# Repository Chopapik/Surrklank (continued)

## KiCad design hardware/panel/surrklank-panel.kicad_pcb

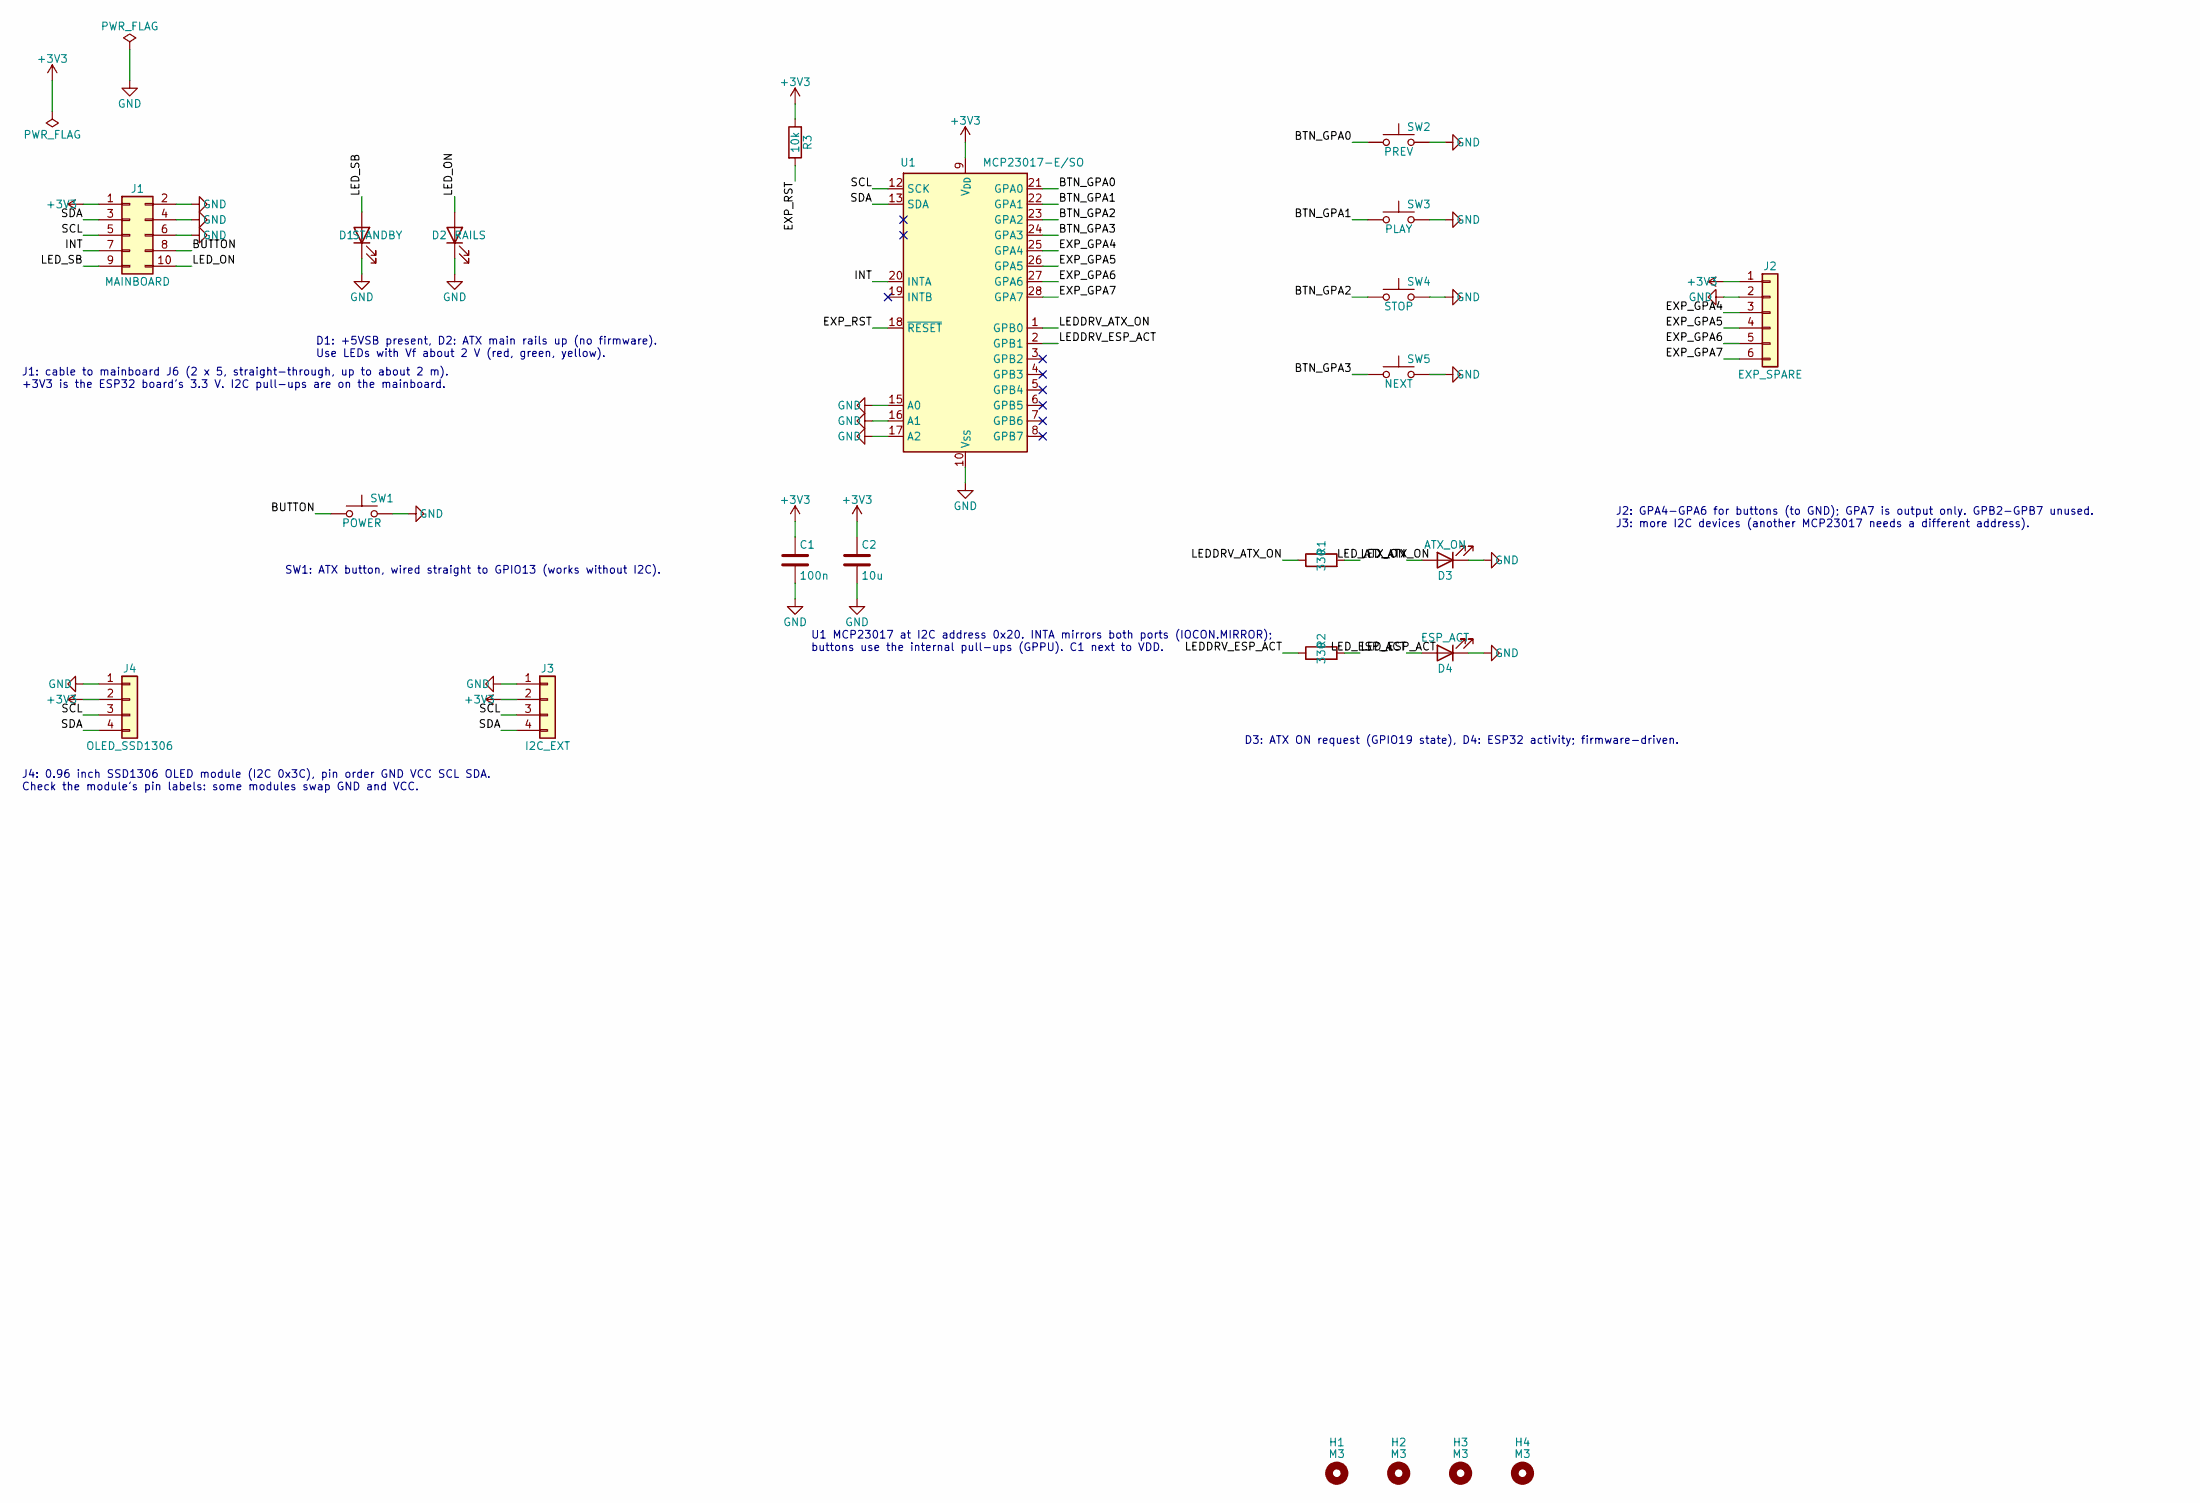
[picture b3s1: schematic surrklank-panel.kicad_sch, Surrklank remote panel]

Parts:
C1: 100n; C_0805_2012Metric
C2: 10u; C_0805_2012Metric
D1: STANDBY; LED_D3.0mm
D2: RAILS; LED_D3.0mm
D3: ATX_ON; LED_D3.0mm
D4: ESP_ACT; LED_D3.0mm
H1, H2, H3, H4: M3; MountingHole_3.2mm_M3
J1: MAINBOARD; IDC-Header_2x05_P2.54mm_Vertical
J2: EXP_SPARE; JST_XH_B6B-XH-A_1x06_P2.50mm_Vertical
J3: I2C_EXT; JST_XH_B4B-XH-A_1x04_P2.50mm_Vertical
J4: OLED_SSD1306; PinSocket_1x04_P2.54mm_Vertical
R1, R2: 330; R_0805_2012Metric
R3: 10k; R_0805_2012Metric
SW1: POWER; SW_PUSH_6mm
SW2: PREV; SW_PUSH_6mm
SW3: PLAY; SW_PUSH_6mm
SW4: STOP; SW_PUSH_6mm
SW5: NEXT; SW_PUSH_6mm
U1: MCP23017-E/SO; SOIC-28W_7.5x17.9mm_P1.27mm

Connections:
+3V3: C1.1, C2.1, J1.1, J2.1, J3.2, J4.2, R3.1, U1.9 (V_{DD})
/BTN_GPA0: SW2.1, U1.21 (GPA0)
/BTN_GPA1: SW3.1, U1.22 (GPA1)
/BTN_GPA2: SW4.1, U1.23 (GPA2)
/BTN_GPA3: SW5.1, U1.24 (GPA3)
/BUTTON: J1.8, SW1.1
/EXP_GPA4: J2.3, U1.25 (GPA4)
/EXP_GPA5: J2.4, U1.26 (GPA5)
/EXP_GPA6: J2.5, U1.27 (GPA6)
/EXP_GPA7: J2.6, U1.28 (GPA7)
/EXP_RST: R3.2, U1.18 (~RESET)
/INT: J1.7, U1.20 (INTA)
/LEDDRV_ATX_ON: R1.1, U1.1 (GPB0)
/LEDDRV_ESP_ACT: R2.1, U1.2 (GPB1)
/LED_ATX_ON: D3.2 (A), R1.2
/LED_ESP_ACT: D4.2 (A), R2.2
/LED_ON: D2.2 (A), J1.10
/LED_SB: D1.2 (A), J1.9
/SCL: J1.5, J3.3, J4.3, U1.12 (SCK)
/SDA: J1.3, J3.4, J4.4, U1.13 (SDA)
GND: C1.2, C2.2, D1.1 (K), D2.1 (K), D3.1 (K), D4.1 (K), J1.2, J1.4, J1.6, J2.2, J3.1, J4.1, SW1.2, SW2.2, SW3.2, SW4.2, SW5.2, U1.10 (V_{SS}), U1.15 (A0), U1.16 (A1), U1.17 (A2)

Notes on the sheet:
J1: cable to mainboard J6 (2 x 5, straight-through, up to about 2 m). +3V3 is the ESP32 board's 3.3 V. I2C pull-ups are on the mainboard.
D1: +5VSB present, D2: ATX main rails up (no firmware). Use LEDs with Vf about 2 V (red, green, yellow).
SW1: ATX button, wired straight to GPIO13 (works without I2C).
U1 MCP23017 at I2C address 0x20. INTA mirrors both ports (IOCON.MIRROR); buttons use the internal pull-ups (GPPU). C1 next to VDD.
D3: ATX ON request (GPIO19 state), D4: ESP32 activity; firmware-driven.
J4: 0.96 inch SSD1306 OLED module (I2C 0x3C), pin order GND VCC SCL SDA. Check the module's pin labels: some modules swap GND and VCC.
J2: GPA4-GPA6 for buttons (to GND); GPA7 is output only. GPB2-GPB7 unused. J3: more I2C devices (another MCP23017 needs a different address).

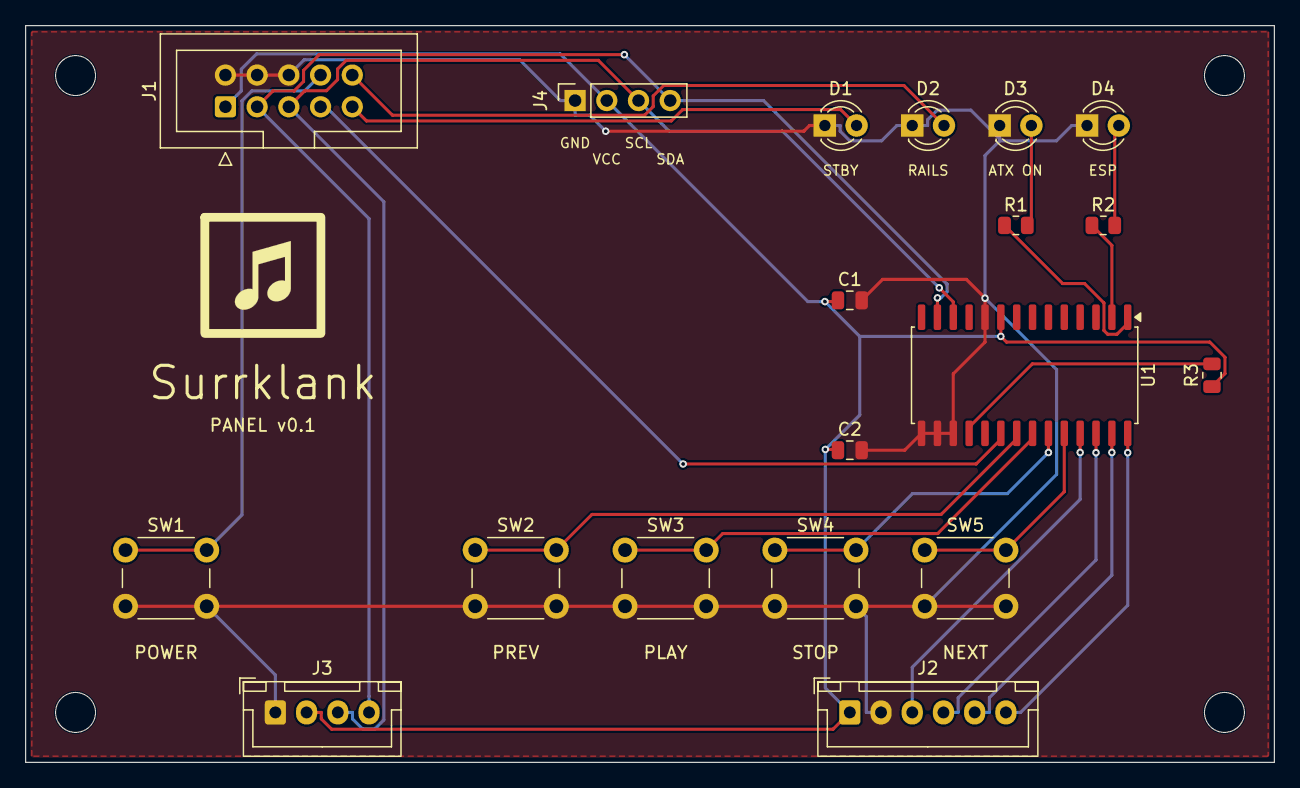
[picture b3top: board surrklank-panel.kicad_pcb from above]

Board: 2 copper layers, 100.0 x 59.0 mm, 25 parts (1 on the bottom side), 21 nets.

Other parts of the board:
LOGO1: Surrklank_Logo; Surrklank_Logo_8mm
LOGO2: Surrklank_Mark; Surrklank_Mark_10mm

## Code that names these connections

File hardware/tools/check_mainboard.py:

#!/usr/bin/env python3
"""Check an exported mainboard netlist against docs/WIRING.md (Mainboard).

Usage: python3 -I check_mainboard.py <netlist.xml>
Rules are written out here independently of the generator.
"""
import sys
import xml.etree.ElementTree as ET

# ESP32 board header (seller pin order; pins 1-19 left, 20-38 right, from the antenna end)
BOARD_PIN = {"GPIO23": "21", "GPIO22": "22", "GPIO34": "5", "GPIO17": "30", "GPIO16": "31",
             "GPIO35": "6", "GPIO18": "28", "GPIO21": "25", "GPIO33": "8", "GPIO32": "7",
             "GPIO19": "27", "GPIO13": "15", "GPIO36": "3", "3V3": "1", "5V": "19",
             "GPIO25": "9", "GPIO26": "10", "GPIO27": "11"}
# WIRING.md GPIO table: GPIO -> (branch connector or None, ribbon pin or role)
SIGNALS = {"GPIO23": ("J2", 1), "GPIO22": ("J2", 5), "GPIO34": ("J2", 13),
           "GPIO17": ("J3", 1), "GPIO16": ("J3", 5), "GPIO35": ("J3", 13)}
SHARED = {"GPIO18": 3, "GPIO21": 7, "GPIO33": 9, "GPIO32": 11}
PULL = {"GPIO21": "ESP_3V3", "GPIO33": "ESP_3V3", "GPIO18": "GND", "GPIO32": "GND",
        "GPIO22": "GND", "GPIO16": "GND", "GPIO23": "GND", "GPIO17": "GND",
        "GPIO34": "GND", "GPIO35": "GND", "GPIO13": "ESP_3V3", "GPIO27": "ESP_3V3"}
errors = []


def main(path):
    root = ET.parse(path).getroot()
    nets, where, func = {}, {}, {}
    for n in root.iter("net"):
        name = n.get("name").lstrip("/")  # local labels are exported as "/NAME"
        nodes = {(x.get("ref"), x.get("pin")) for x in n.iter("node")}
        nets[name] = nodes
        for x in n.iter("node"):
            where[(x.get("ref"), x.get("pin"))] = name
            func[(x.get("ref"), x.get("pin"))] = (x.get("pinfunction") or "").split("_")[0]

    def peers(ref, pin):
        return nets.get(where.get((ref, pin)), set()) - {(ref, pin)}

    def through(rn, pin):
        """Net on the other side of a resistor-array element."""
        return where.get((rn, str(9 - int(pin))))

    def gpio_net(g):
        return where.get(("A1", BOARD_PIN[g]))

    def reaches_via_series(g, conn, rpin):
        for r, q in peers("A1", BOARD_PIN[g]):
            if r.startswith("RN") and through(r, q) == where.get((conn, str(rpin))):
                return True
        return False

    def reaches_via_resistor(g, conn, rpin):
        """Single resistor between the GPIO and the connector pin (Q165 return)."""
        target = where.get((conn, str(rpin)))
        for r, q in peers("A1", BOARD_PIN[g]):
            if r.startswith("R") and not r.startswith("RN") \
                    and where.get((r, "2" if q == "1" else "1")) == target:
                return True
        return False

    for g, (conn, rpin) in SIGNALS.items():
        if rpin == 13:
            if not reaches_via_resistor(g, conn, rpin):
                errors.append(f"{g} must reach {conn}.13 (Q165) through a series resistor")
        elif not reaches_via_series(g, conn, rpin):
            errors.append(f"{g} must reach {conn}.{rpin} through a series resistor")
    for g, rpin in SHARED.items():
        for conn in ("J2", "J3"):
            if not reaches_via_series(g, conn, rpin):
                errors.append(f"{g} must reach {conn}.{rpin} through its own series resistor")
    for g, rail in PULL.items():
        rails = [through(r, q) for r, q in peers("A1", BOARD_PIN[g])
                 if r.startswith("RN") and through(r, q) in ("ESP_3V3", "GND")]
        if rails != [rail]:
            errors.append(f"{g}: expected one pull to {rail}, got {rails}")
    for conn in ("J2", "J3"):
        for p in range(2, 17, 2):
            if where.get((conn, str(p))) != "GND":
                errors.append(f"{conn}.{p} should be GND")
        if peers(conn, "15"):
            errors.append(f"{conn}.15 is a spare wire and must stay unconnected")

    if "+3V3" in nets or any(r.startswith("JP") and r != "JP1" for r, _ in where):
        errors.append("ATX +3V3 and the bench jumpers are removed")
    if gpio_net("3V3") != "ESP_3V3" or gpio_net("3V3") in ("+5V", "ATX_5VSB"):
        errors.append("ESP32 3V3 must stay separate from ATX +5V and +5VSB")
    # +5VSB path: terminal pin 4 -> removable jumper -> ESP32 5V, nothing else
    j1 = {p: where.get(("J1", p)) for p in "1234"}
    if [j1[p] for p in "1234"] != ["GND", "PS_ON#", "ATX_5VSB", "PWR_OK"] or ("J1", "5") in where:
        errors.append(f"J1 order wrong: {j1}")
    # +5VSB may also feed the panel standby LED resistor (checked below)
    on_5vsb = {(r, q) for r, q in nets.get("ATX_5VSB", set()) - {("J1", "3")}
               if r != "Q2" and not (r.startswith("R") and where.get((r, "2" if q == "1" else "1"))
                                     == where.get(("J6", "9")))}
    if len(on_5vsb) != 1 or not next(iter(on_5vsb))[0].startswith("JP"):
        errors.append(f"+5VSB must go only to one removable jumper, got {sorted(on_5vsb)}")
    else:
        jp = next(iter(on_5vsb))[0]
        if "ESP_5V" not in {where.get((jp, q)) for q in ("1", "2")}:
            errors.append("+5VSB jumper must lead to ESP32 5V")
    if gpio_net("5V") != "ESP_5V":
        errors.append("ESP32 5V pin must be on ESP_5V")
    # PWR_OK divider into GPIO36
    rs = [r for r, _ in nets.get("PWR_OK", set()) if r.startswith("R")
          and gpio_net("GPIO36") in {where.get((r, q)) for q in ("1", "2")}]
    if len(rs) != 1:
        errors.append("PWR_OK must reach GPIO36 through a series resistor")
    # ATX switch: GPIO19 -> R -> base, base -> R -> GND, emitter GND, collector PS_ON#
    q = next(r for r, _ in nets["PS_ON#"] if r.startswith("Q"))
    pins = {func[(q, p)]: where[(q, p)] for p in ("1", "2", "3")}
    if pins.get("C") != "PS_ON#" or pins.get("E") != "GND":
        errors.append(f"transistor pins wrong: {pins}")
    base = nets[pins["B"]]
    if not any(r.startswith("R") and gpio_net("GPIO19") in {where.get((r, x)) for x in ("1", "2")}
               for r, _ in base):
        errors.append("GPIO19 must drive the base through a resistor")
    if not any(r.startswith("R") and "GND" in {where.get((r, x)) for x in ("1", "2")} for r, _ in base):
        errors.append("base needs a resistor to GND")
    if {where.get(("J4", "1")), where.get(("J4", "2"))} != {gpio_net("GPIO13"), "GND"}:
        errors.append("button J4 must connect GPIO13 to GND")
    if not any(r.startswith("C") and "GND" in {where.get((r, x)) for x in ("1", "2")}
               for r, _ in peers("A1", BOARD_PIN["GPIO13"])):
        errors.append("button line needs a filter capacitor to GND")

    # Remote panel J6 (2 x 5): 1 ESP_3V3, 2/4/6 GND, 3 SDA, 5 SCL, 7 INT, 8 button,
    # 9 LED from +5VSB, 10 LED from ATX +5V (each through a resistor)
    if where.get(("J6", "1")) != gpio_net("3V3"):
        errors.append("J6.1 must be the ESP32 3V3")
    for p in ("2", "4", "6"):
        if where.get(("J6", p)) != "GND":
            errors.append(f"J6.{p} should be GND")
    for g, p in (("GPIO25", "3"), ("GPIO26", "5"), ("GPIO27", "7"), ("GPIO13", "8")):
        if where.get(("J6", p)) != gpio_net(g):
            errors.append(f"J6.{p} must connect directly to {g}")
    for g in ("GPIO25", "GPIO26"):
        ups = [r for r, q in peers("A1", BOARD_PIN[g]) if r.startswith("R") and not r.startswith("RN")
               and where.get((r, "2" if q == "1" else "1")) == gpio_net("3V3")]
        if len(ups) != 1:
            errors.append(f"{g} (I2C) needs one pull-up to the ESP32 3V3")
    feed = [r for r, q in peers("J6", "9") if r.startswith("R") and not r.startswith("RN")
            and where.get((r, "2" if q == "1" else "1")) == "ATX_5VSB"]
    if len(feed) != 1 or len(peers("J6", "9")) != 1:
        errors.append("J6.9 must be fed only through one resistor from ATX_5VSB")
    # J6.10: one resistor from the emitter of Q2 (collector +5VSB, base from PWR_OK via a resistor)
    feed = [(r, q) for r, q in peers("J6", "10") if r.startswith("R") and not r.startswith("RN")]
    if len(feed) != 1 or len(peers("J6", "10")) != 1:
        errors.append("J6.10 must be fed only through one resistor")
    else:
        r, q = feed[0]
        drv = where.get((r, "2" if q == "1" else "1"))
        q2 = {func[("Q2", p)]: where[("Q2", p)] for p in ("1", "2", "3")}
        if q2.get("E") != drv or q2.get("C") != "ATX_5VSB":
            errors.append(f"Q2 must be an emitter follower on +5VSB feeding J6.10, got {q2}")
        elif not any(r2.startswith("R") and "PWR_OK" in {where.get((r2, x)) for x in ("1", "2")}
                     for r2, _ in nets[q2["B"]]):
            errors.append("Q2 base must be driven from PWR_OK through a resistor")

    if errors:
        print(f"{len(errors)} problem(s):")
        for e in errors:
            print("  -", e)
        sys.exit(1)
    print("OK: netlist matches WIRING.md rules")


if __name__ == "__main__":
    main(sys.argv[1])
